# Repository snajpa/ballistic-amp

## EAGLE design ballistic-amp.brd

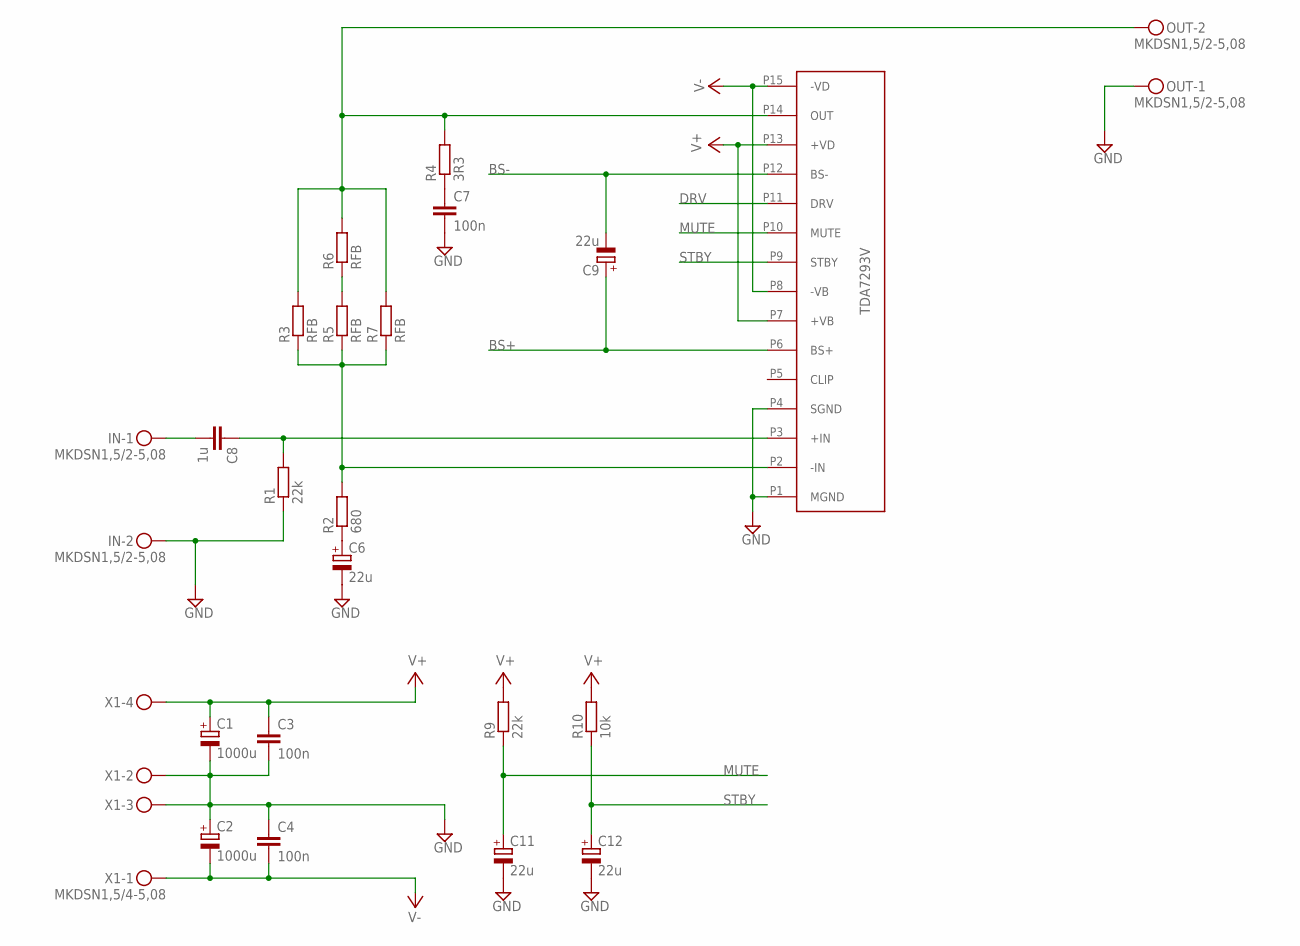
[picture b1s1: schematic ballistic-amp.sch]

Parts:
C1, C2: 1000u; E7,5-18
C3, C4, C7: 100n; C050-025X075
C6, C9: 22u; E5-10,5
C8: 1u; C1210
C11, C12: 22u; UD-6,3X7,7_NICHICON
IN: MKDSN1,5/2-5,08
OUT: MKDSN1,5/2-5,08
R1, R9: 22k; 0207/10
R2: 680; 0207/10
R3, R5, R6, R7: RFB; 0207/10
R4: 3R3; R2512
R10: 10k; 0207/10
U$1: TDA7293V
X1: MKDSN1,5/4-5,08

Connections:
BS+: C9.+, U$1.P6 (BS+)
BS-: C9.-, U$1.P12 (BS-)
DRV: U$1.P11 (DRV)
GND: C1.-, C2.+, C3.2, C4.1, C6.-, C7.2, C11.-, C12.-, IN.2, OUT.1, R1.1, U$1.P1 (MGND), U$1.P4 (SGND), X1.2, X1.3
MUTE: C11.+, R9.1, U$1.P10 (MUTE)
unnamed: C6.+, R2.1
unnamed: R2.2, R3.1, R5.1, R7.1, U$1.P2 (-IN)
unnamed: C7.1, R4.1
unnamed: C8.2, IN.1
unnamed: C8.1, R1.2, U$1.P3 (+IN)
unnamed: OUT.2, R3.2, R4.2, R6.2, R7.2, U$1.P14 (OUT)
unnamed: R5.2, R6.1
STBY: C12.+, R10.1, U$1.P9 (STBY)
V+: C1.+, C3.1, R9.2, R10.2, U$1.P7 (+VB), U$1.P13 (+VD), X1.4
V-: C2.-, C4.2, U$1.P8 (-VB), U$1.P15 (-VD), X1.1

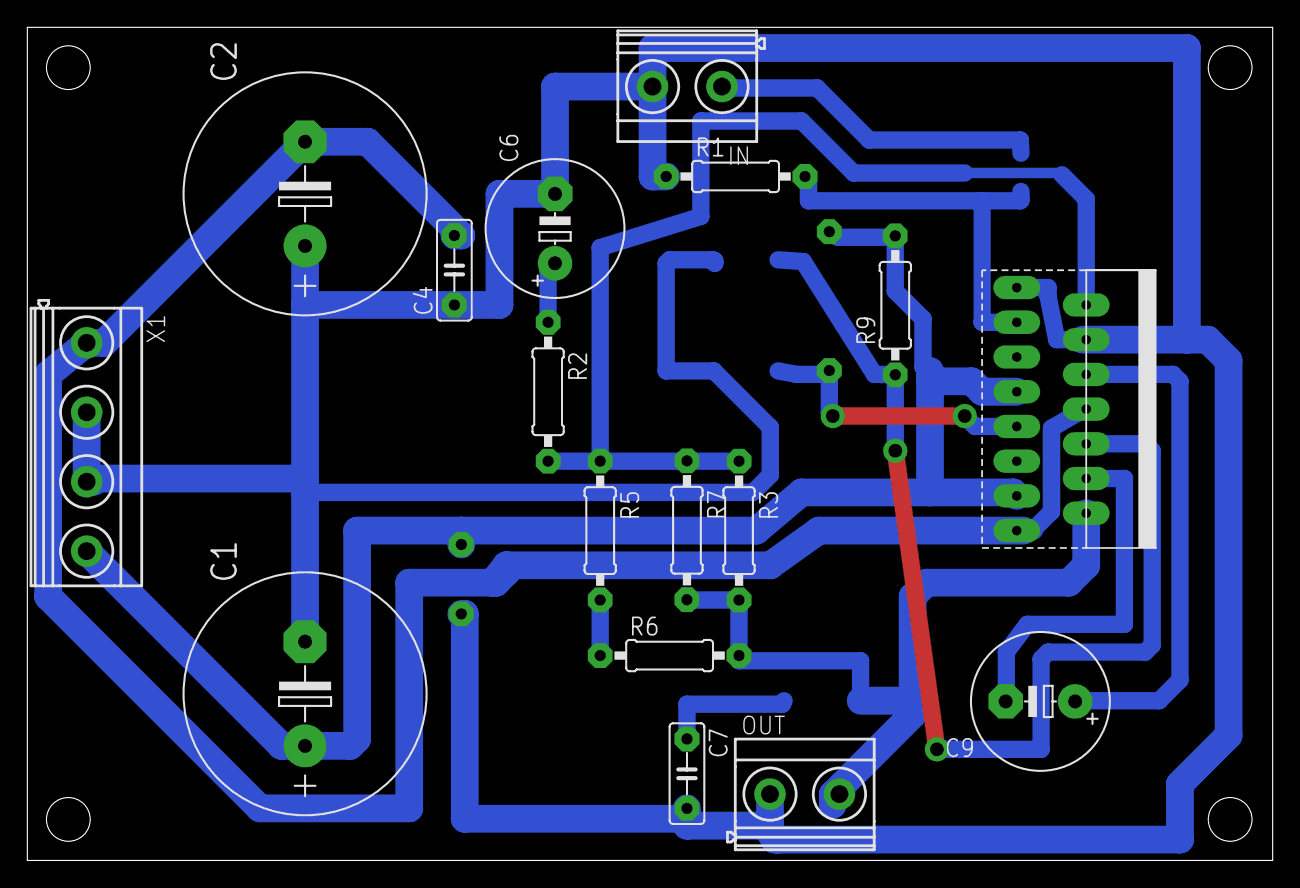
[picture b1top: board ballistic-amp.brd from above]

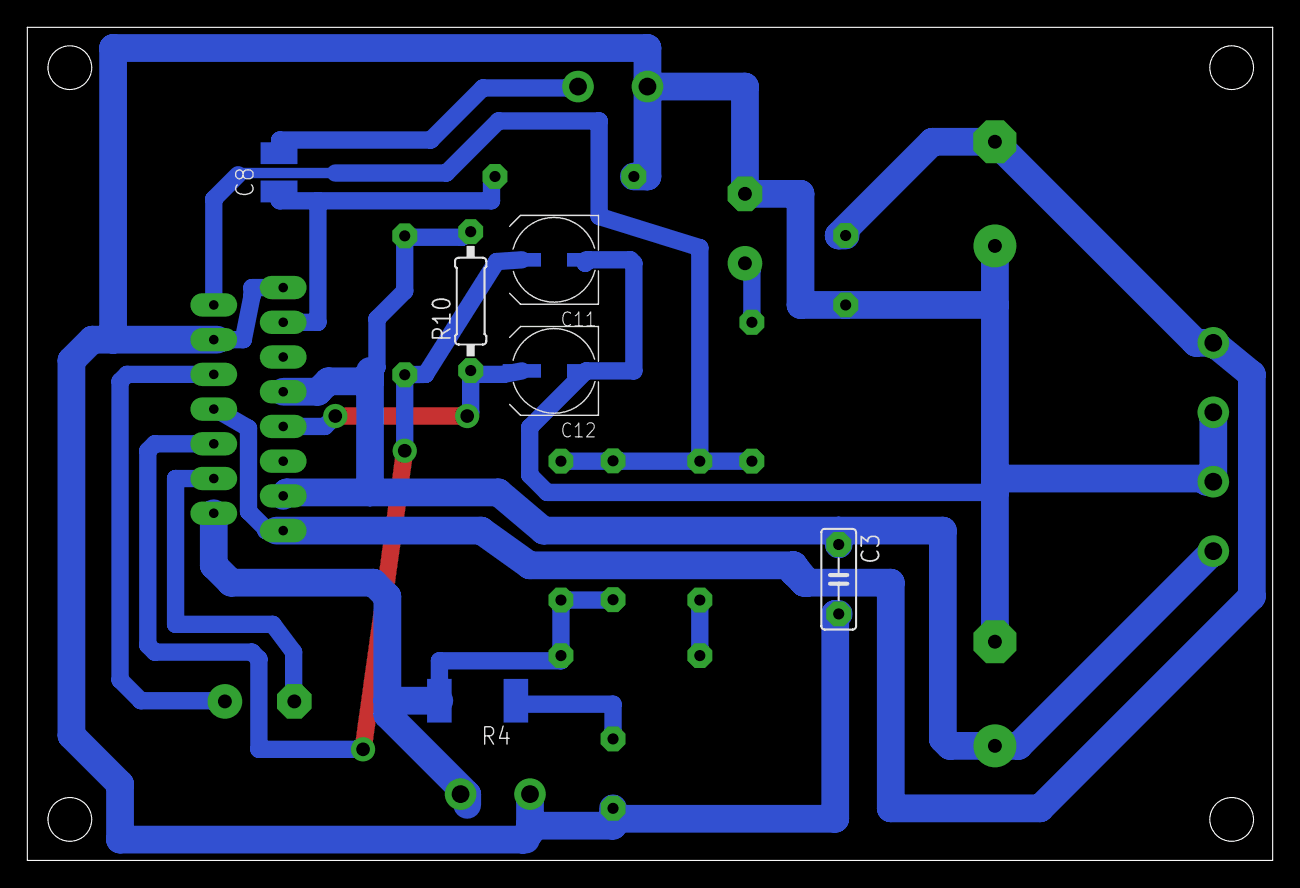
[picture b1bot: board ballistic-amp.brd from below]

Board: 2 copper layers, 91.1 x 61.0 mm, 23 parts (6 on the bottom side), 14 nets.

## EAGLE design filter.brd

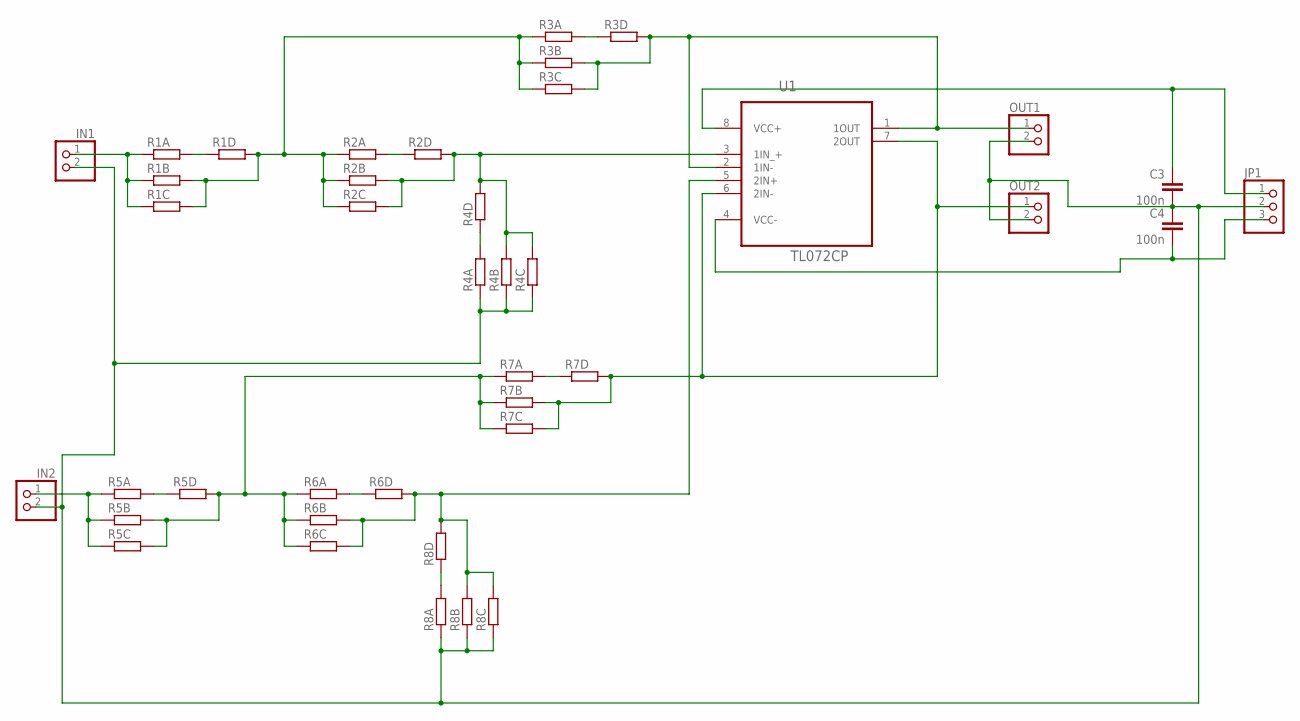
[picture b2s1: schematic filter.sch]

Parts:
C3, C4: 100n; C1206
IN1, IN2: PINHD-1X2; 1X02
JP1: PINHD-1X3; 1X03
OUT1, OUT2: PINHD-1X2; 1X02
R1A, R1B, R1C, R1D, R2A, R2B, R2C, R2D, R3A, R3B, R3C, R3D, R4A, R4B, R4C, R4D, R5A, R5B, R5C, R5D, R6A, R6B, R6C, R6D, R7A, R7B, R7C, R7D, R8A, R8B, R8C, R8D: R-EU_0207/10; 0207/10
U1: TL072CP; DIP254P762X508-8

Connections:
unnamed: IN1.1, R1A.1, R1B.1, R1C.1
unnamed: R6B.2, R6C.2, R6D.2, R8B.2, R8C.2, R8D.2, U1.5 (2IN+)
unnamed: OUT2.1, R7B.2, R7C.2, R7D.2, U1.6 (2IN-), U1.7 (2OUT)
unnamed: C4.2, JP1.3, U1.4 (VCC-)
unnamed: C3.1, JP1.1, U1.8 (VCC+)
unnamed: OUT1.1, R3B.2, R3C.2, R3D.2, U1.1 (1OUT), U1.2 (1IN-)
unnamed: R1A.2, R1D.1
unnamed: R2B.2, R2C.2, R2D.2, R4B.2, R4C.2, R4D.2, U1.3 (1IN_+)
unnamed: R2A.2, R2D.1
unnamed: C3.2, C4.1, IN1.2, IN2.2, JP1.2, OUT1.2, OUT2.2, R4A.1, R4B.1, R4C.1, R8A.1, R8B.1, R8C.1
unnamed: R4A.2, R4D.1
unnamed: R1B.2, R1C.2, R1D.2, R2A.1, R2B.1, R2C.1, R3A.1, R3B.1, R3C.1
unnamed: R3A.2, R3D.1
unnamed: IN2.1, R5A.1, R5B.1, R5C.1
unnamed: R5A.2, R5D.1
unnamed: R6A.2, R6D.1
unnamed: R8A.2, R8D.1
unnamed: R5B.2, R5C.2, R5D.2, R6A.1, R6B.1, R6C.1, R7A.1, R7B.1, R7C.1
unnamed: R7A.2, R7D.1

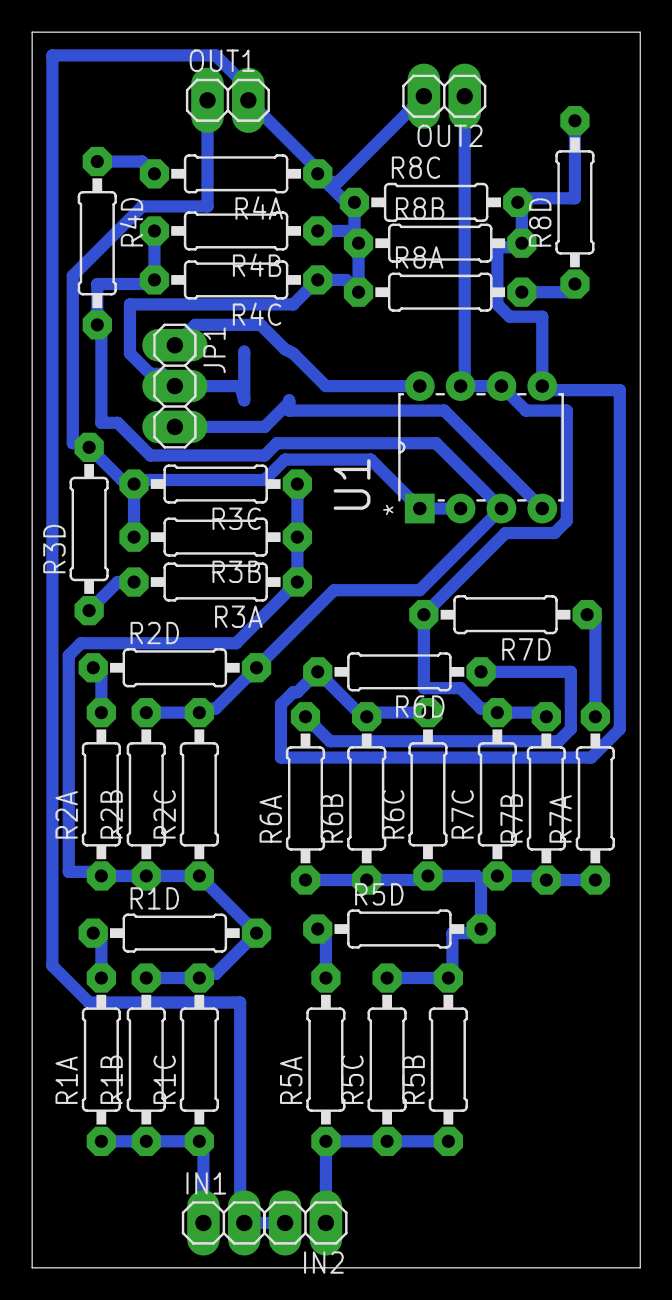
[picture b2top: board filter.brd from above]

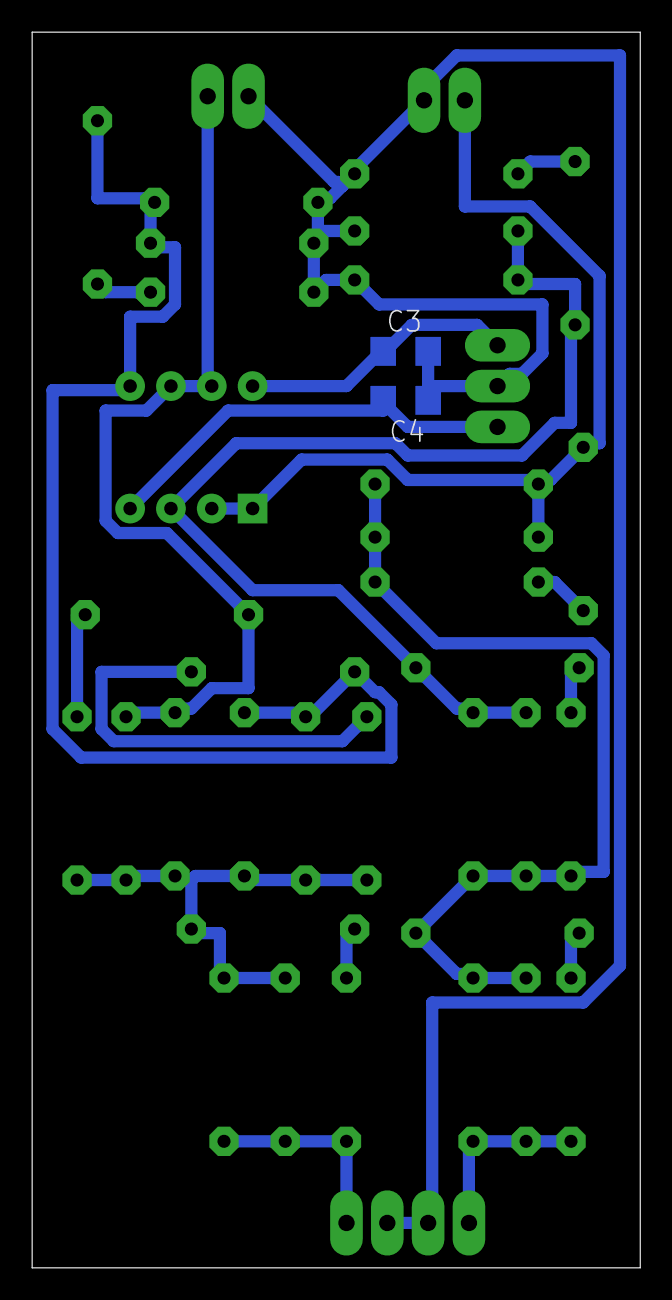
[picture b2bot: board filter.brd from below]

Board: 2 copper layers, 37.8 x 76.9 mm, 40 parts (2 on the bottom side), 19 nets.

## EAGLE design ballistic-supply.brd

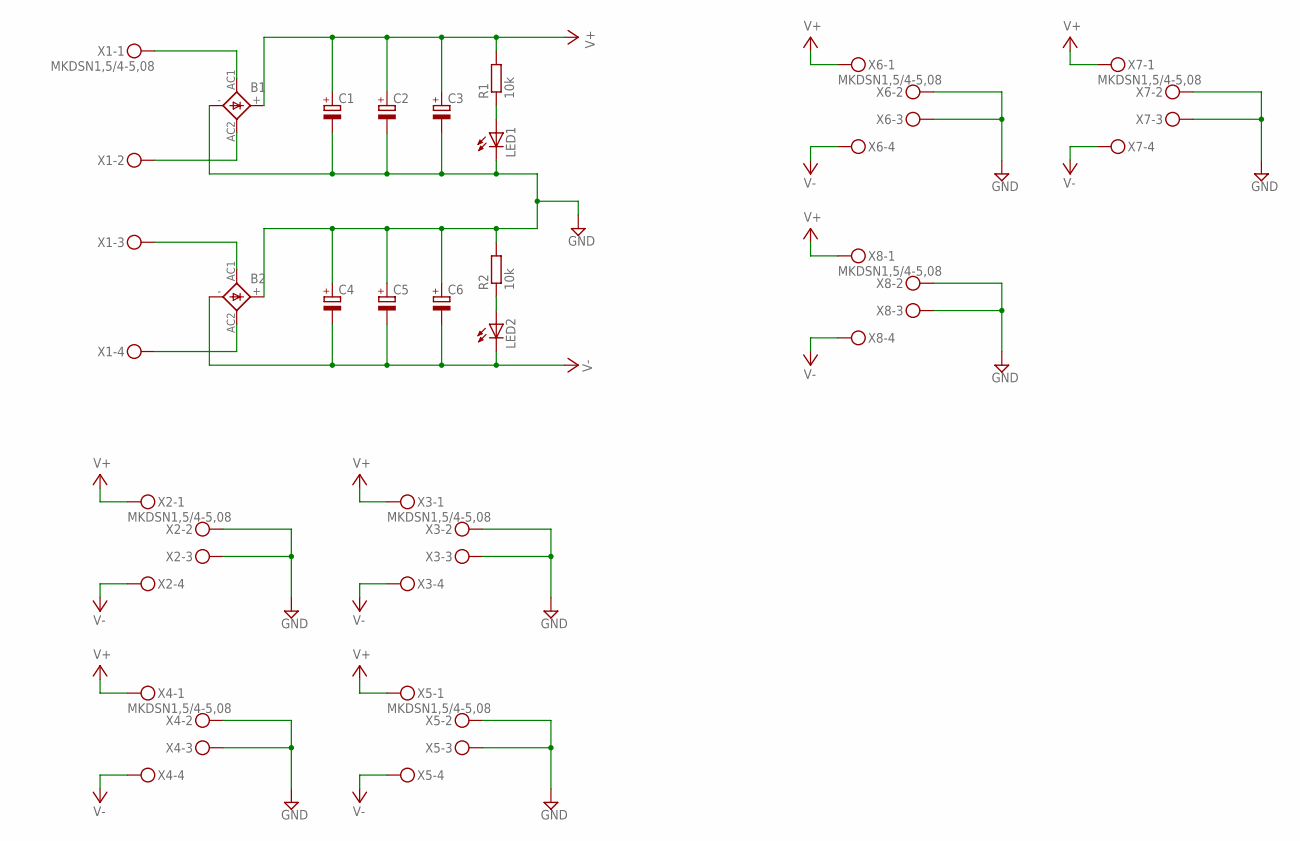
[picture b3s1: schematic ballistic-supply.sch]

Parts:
B1, B2: SKB32
C1, C2, C3, C4, C5, C6: CPOL-EUE7.5-18; E7,5-18
LED1, LED2: LEDSMT1206; 1206
R1, R2: 10k; M1206
X1, X2, X3, X4, X5, X6, X7, X8: MKDSN1,5/4-5,08

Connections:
GND: B1.-, B2.+, C1.-, C2.-, C3.-, C4.+, C5.+, C6.+, LED1.C, R2.2, X2.2, X2.3, X3.2, X3.3, X4.2, X4.3, X5.2, X5.3, X6.2, X6.3, X7.2, X7.3, X8.2, X8.3
unnamed: B1.AC1, X1.1
unnamed: B1.AC2, X1.2
unnamed: B2.AC1, X1.3
unnamed: B2.AC2, X1.4
unnamed: LED2.A, R2.1
unnamed: LED1.A, R1.1
V+: B1.+, C1.+, C2.+, C3.+, R1.2, X2.1, X3.1, X4.1, X5.1, X6.1, X7.1, X8.1
V-: B2.-, C4.-, C5.-, C6.-, LED2.C, X2.4, X3.4, X4.4, X5.4, X6.4, X7.4, X8.4

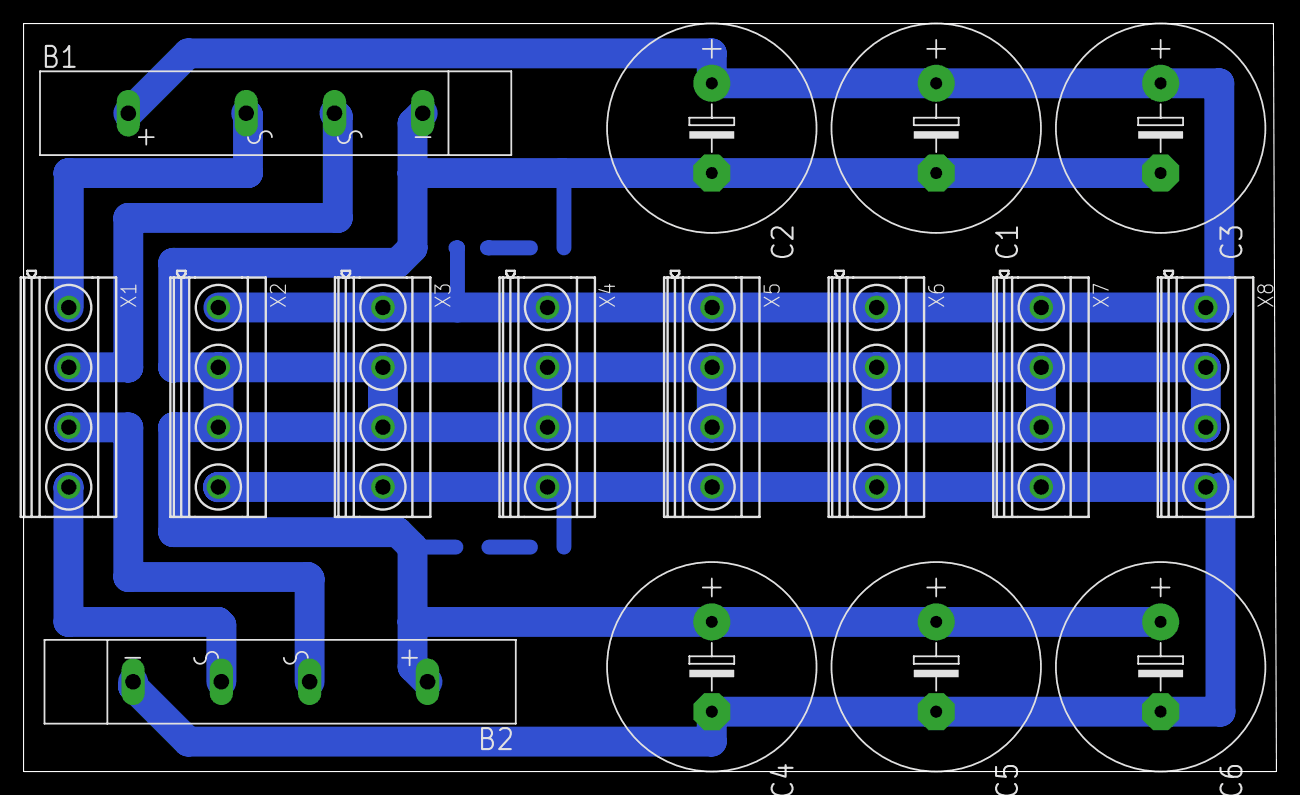
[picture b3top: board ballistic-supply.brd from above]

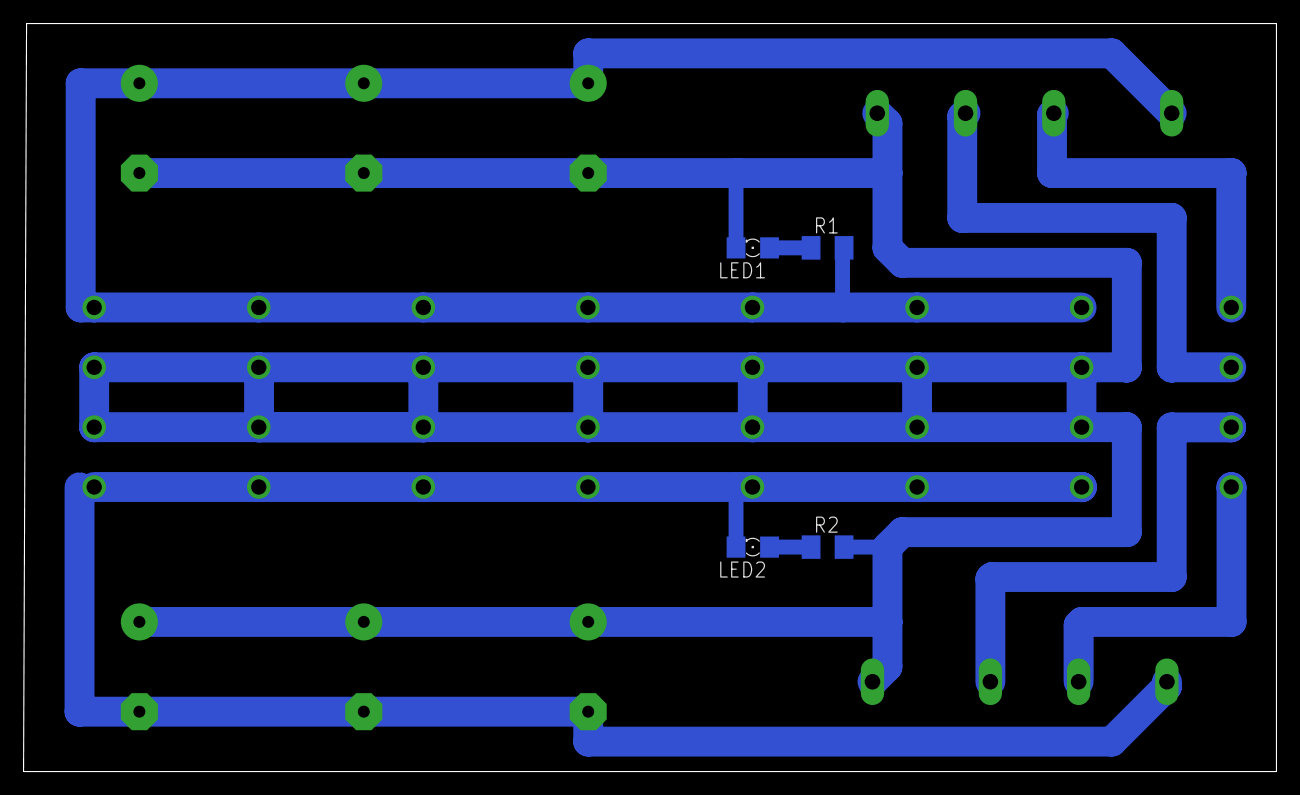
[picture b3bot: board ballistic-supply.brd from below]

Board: 2 copper layers, 106.3 x 63.5 mm, 20 parts (4 on the bottom side), 9 nets.

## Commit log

2016-12-08 dem filez
2016-12-08 amp sch png
